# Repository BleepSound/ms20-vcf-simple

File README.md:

[![CC BY-SA 4.0][cc-by-sa-shield]][cc-by-sa]

# MS20 VCF

Latest documentation available at https://bleepsound.github.io/modules/

[![CC BY-SA 4.0][cc-by-sa-image]][cc-by-sa]

[cc-by-sa]: http://creativecommons.org/licenses/by-sa/4.0/
[cc-by-sa-image]: https://licensebuttons.net/l/by-sa/4.0/88x31.png
[cc-by-sa-shield]: https://img.shields.io/badge/License-CC%20BY--SA%204.0-lightgrey.svg

[![CC BY-SA 4.0][cc-by-sa-shield]][cc-by-sa]

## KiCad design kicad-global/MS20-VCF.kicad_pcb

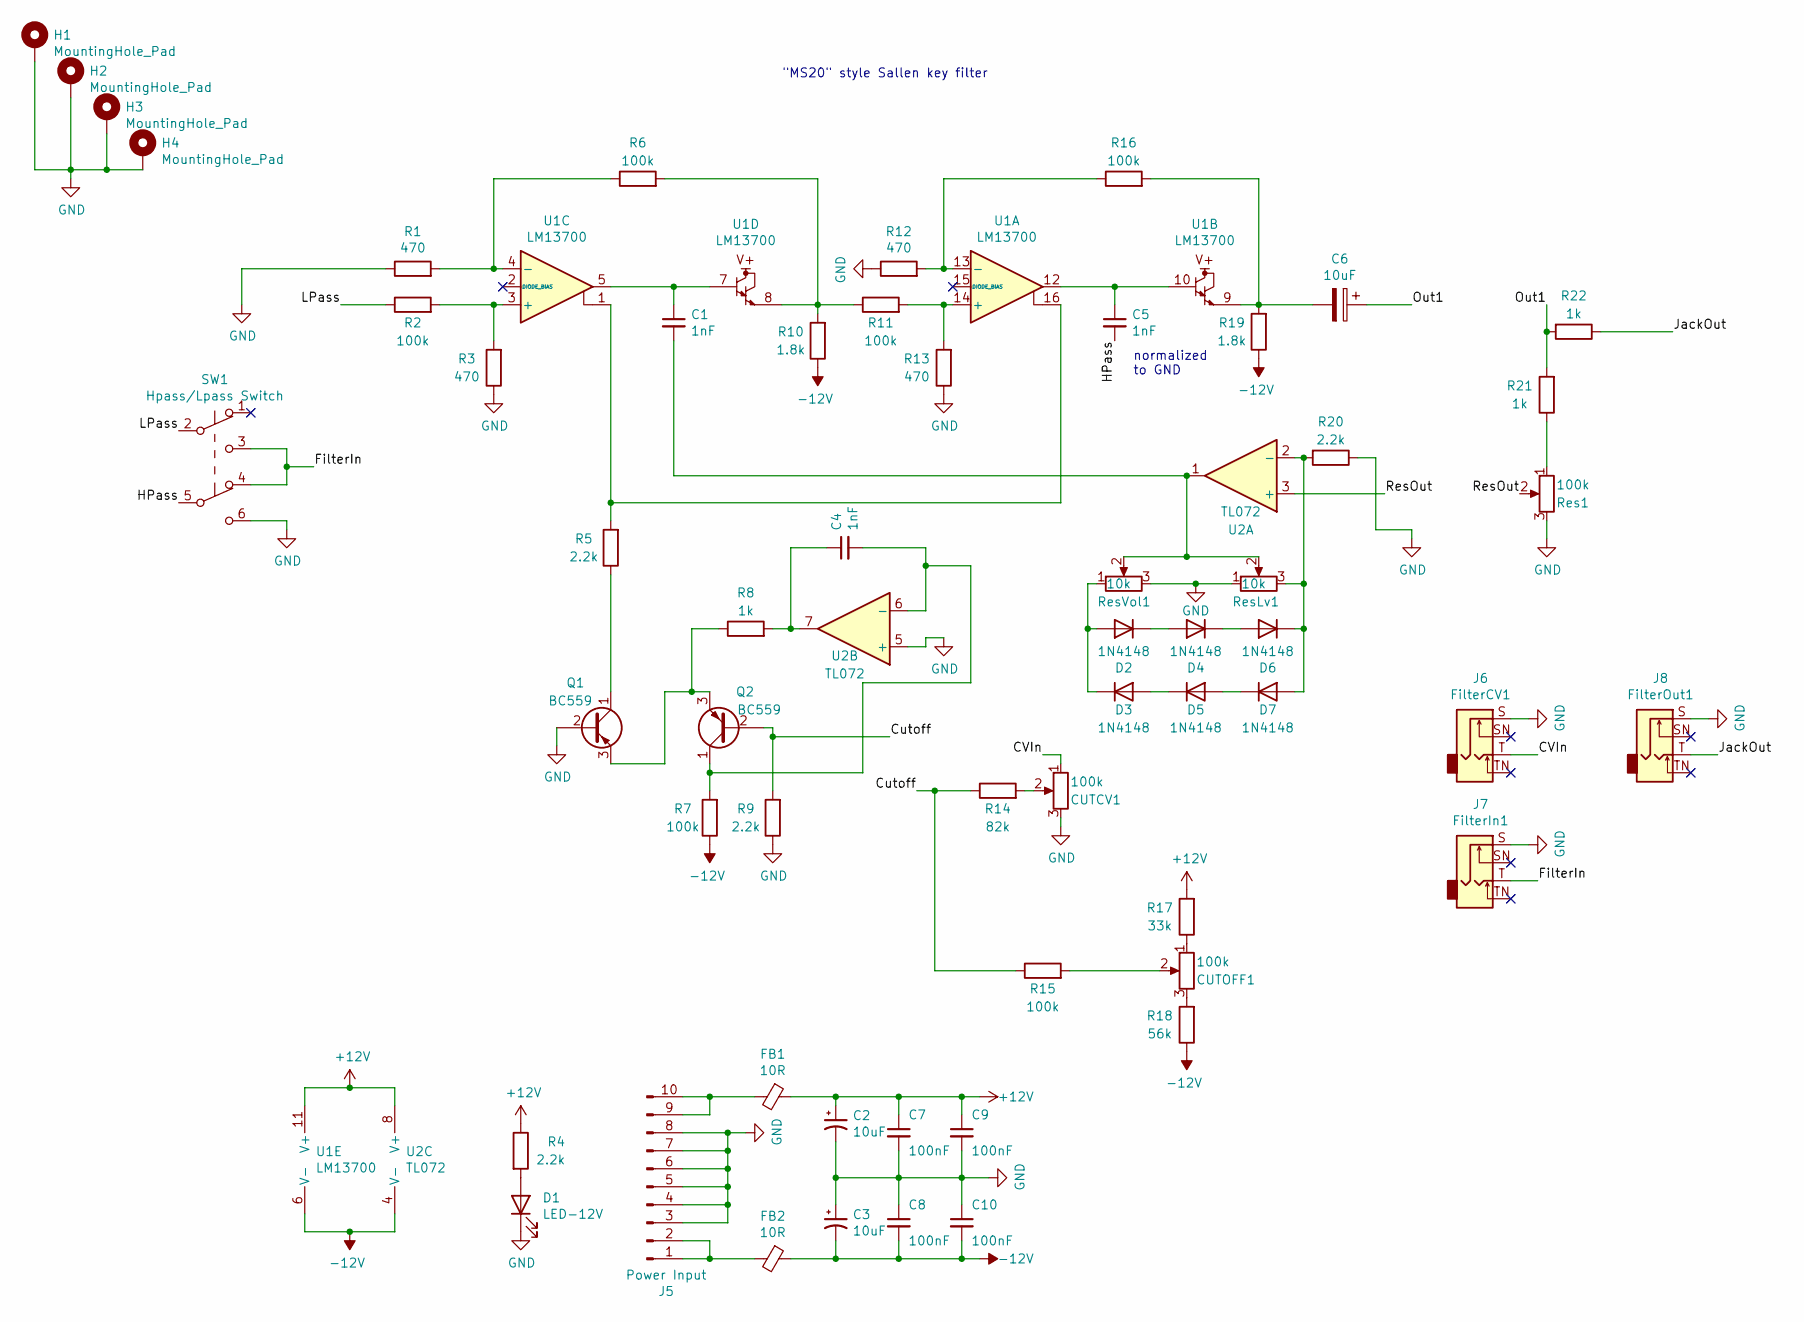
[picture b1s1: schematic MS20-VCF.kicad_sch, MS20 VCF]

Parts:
C1, C4, C5: 1nF; C_Disc_D7.0mm_W2.5mm_P5.00mm
C2, C3, C6: 10uF; CP_Radial_D5.0mm_P2.00mm
C7, C8, C9, C10: 100nF; C_Disc_D7.0mm_W2.5mm_P5.00mm
CUTCV1: 100k; Pot-bourns-alpha
CUTOFF1: 100k; Pot-bourns-alpha
D1: LED-12V; LED_D4.0mm
D2, D3, D4, D5, D6, D7: 1N4148; D_DO-35_SOD27_P7.62mm_Horizontal
FB1, FB2: 10R; L_Axial_L9.5mm_D4.0mm_P12.70mm_Horizontal_Fastron_SMCC
H1, H2, H3, H4: MountingHole_Pad; Doepfer Mounting hole
J5: Power Input; IDC-Header_2x05_P2.54mm_Vertical
J6: FilterCV1; Thonkiconn
J7: FilterIn1; Thonkiconn
J8: FilterOut1; Thonkiconn
Q1, Q2: BC559; TO-92_Inline_Wide
R1, R3, R12, R13: 470; R_Axial_DIN0207_L6.3mm_D2.5mm_P10.16mm_Horizontal
R2, R6, R7, R11, R15, R16: 100k; R_Axial_DIN0207_L6.3mm_D2.5mm_P10.16mm_Horizontal
R4, R5, R9, R20: 2.2k; R_Axial_DIN0207_L6.3mm_D2.5mm_P10.16mm_Horizontal
R8, R21, R22: 1k; R_Axial_DIN0207_L6.3mm_D2.5mm_P10.16mm_Horizontal
R10, R19: 1.8k; R_Axial_DIN0207_L6.3mm_D2.5mm_P10.16mm_Horizontal
R14: 82k; R_Axial_DIN0207_L6.3mm_D2.5mm_P10.16mm_Horizontal
R17: 33k; R_Axial_DIN0207_L6.3mm_D2.5mm_P10.16mm_Horizontal
R18: 56k; R_Axial_DIN0207_L6.3mm_D2.5mm_P10.16mm_Horizontal
Res1: 100k; Pot-bourns-alpha
ResLv1: 10k; Potentiometer_Bourns_3386C_Horizontal
ResVol1: 10k; Potentiometer_Bourns_3386C_Horizontal
SW1: Hpass/Lpass Switch; SW_DPDT_Toggle
U1: LM13700; SOIC-16_3.9x9.9mm_P1.27mm
U2: TL072; DIP-8_W7.62mm_Socket

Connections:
+12V: C2.1, C7.1, C9.1, FB1.1, R4.1, R17.2, U1.11 (V+), U2.8 (V+)
-12V: C3.2, C8.2, C10.2, FB2.1, R7.1, R10.1, R18.1, R19.1, U1.6 (V-), U2.4 (V-)
/CVIn: CUTCV1.1, J6.T
/Cutoff: Q2.2 (B), R9.2, R14.1, R15.1
/FilterIn: J7.T, SW1.3 (C), SW1.4 (A)
/HPass: C5.2, SW1.5 (B)
/JackOut: J8.T, R22.1
/LPass: R2.1, SW1.2 (B)
/Out1: C6.1, R21.2, R22.2
/ResOut: Res1.2, U2.3 (+)
GND: C2.2, C3.1, C7.2, C8.1, C9.2, C10.1, CUTCV1.3, D1.1 (K), H1.1, H2.1, H3.1, H4.1, J5.3, J5.4, J5.5, J5.6, J5.7, J5.8, J6.S, J7.S, J8.S, Q1.2 (B), R1.1, R3.1, R9.1, R12.1, R13.1, R20.1, Res1.3, ResLv1.1, ResVol1.3, SW1.6 (C), U2.5 (+)
unnamed: C1.1, U1.5, U1.7
unnamed: C1.2, ResLv1.2, ResVol1.2, U2.1
unnamed: C4.1, R8.2, U2.7
unnamed: C4.2, Q2.1 (C), R7.2, U2.6 (-)
unnamed: C5.1, U1.10, U1.12
unnamed: C6.2, R16.2, R19.2, U1.9
unnamed: CUTCV1.2, R14.2
unnamed: CUTOFF1.1, R17.1
unnamed: CUTOFF1.2, R15.2
unnamed: CUTOFF1.3, R18.2
unnamed: D1.2 (A), R4.2
unnamed: D2.1 (K), D4.2 (A)
unnamed: D2.2 (A), D3.1 (K), ResVol1.1
unnamed: D3.2 (A), D5.1 (K)
unnamed: D4.1 (K), D6.2 (A)
unnamed: D5.2 (A), D7.1 (K)
unnamed: D6.1 (K), D7.2 (A), R20.2, ResLv1.3, U2.2 (-)
unnamed: FB1.2, J5.9, J5.10
unnamed: FB2.2, J5.1, J5.2
unnamed: Q1.1 (C), R5.1
unnamed: Q1.3 (E), Q2.3 (E), R8.1
unnamed: R1.2, R6.1, U1.4 (-)
unnamed: R2.2, R3.2, U1.3 (+)
unnamed: R5.2, U1.1, U1.16
unnamed: R6.2, R10.2, R11.1, U1.8
unnamed: R11.2, R13.2, U1.14 (+)
unnamed: R12.2, R16.1, U1.13 (-)
unnamed: R21.1, Res1.1

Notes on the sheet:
normalized to GND
"MS20" style Sallen key filter

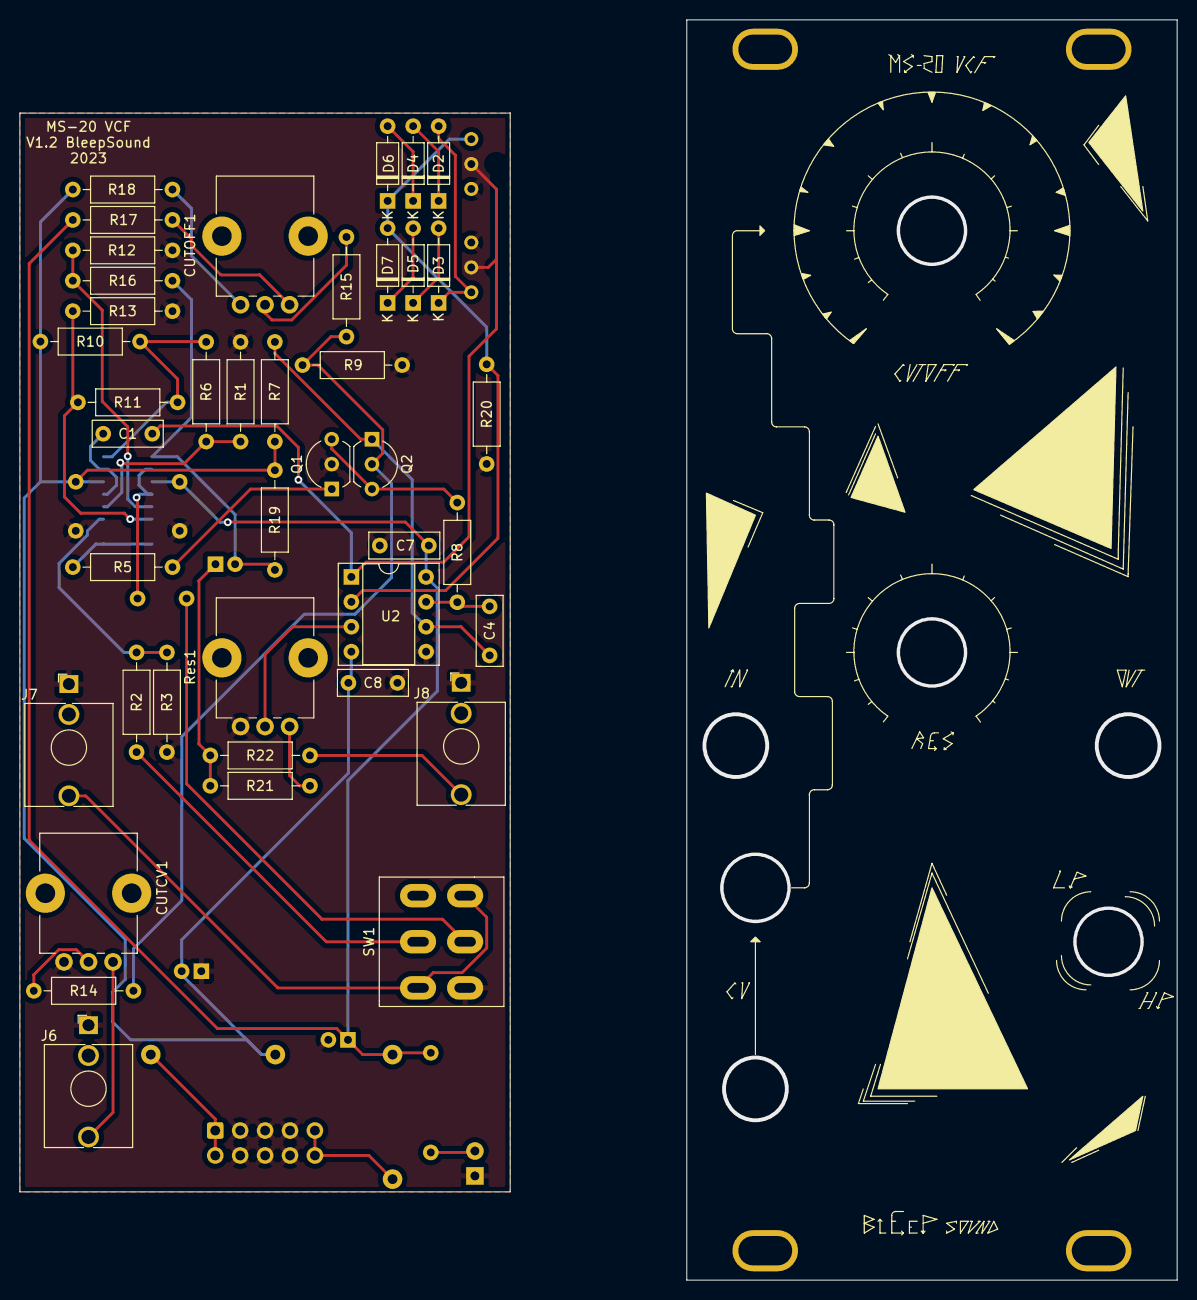
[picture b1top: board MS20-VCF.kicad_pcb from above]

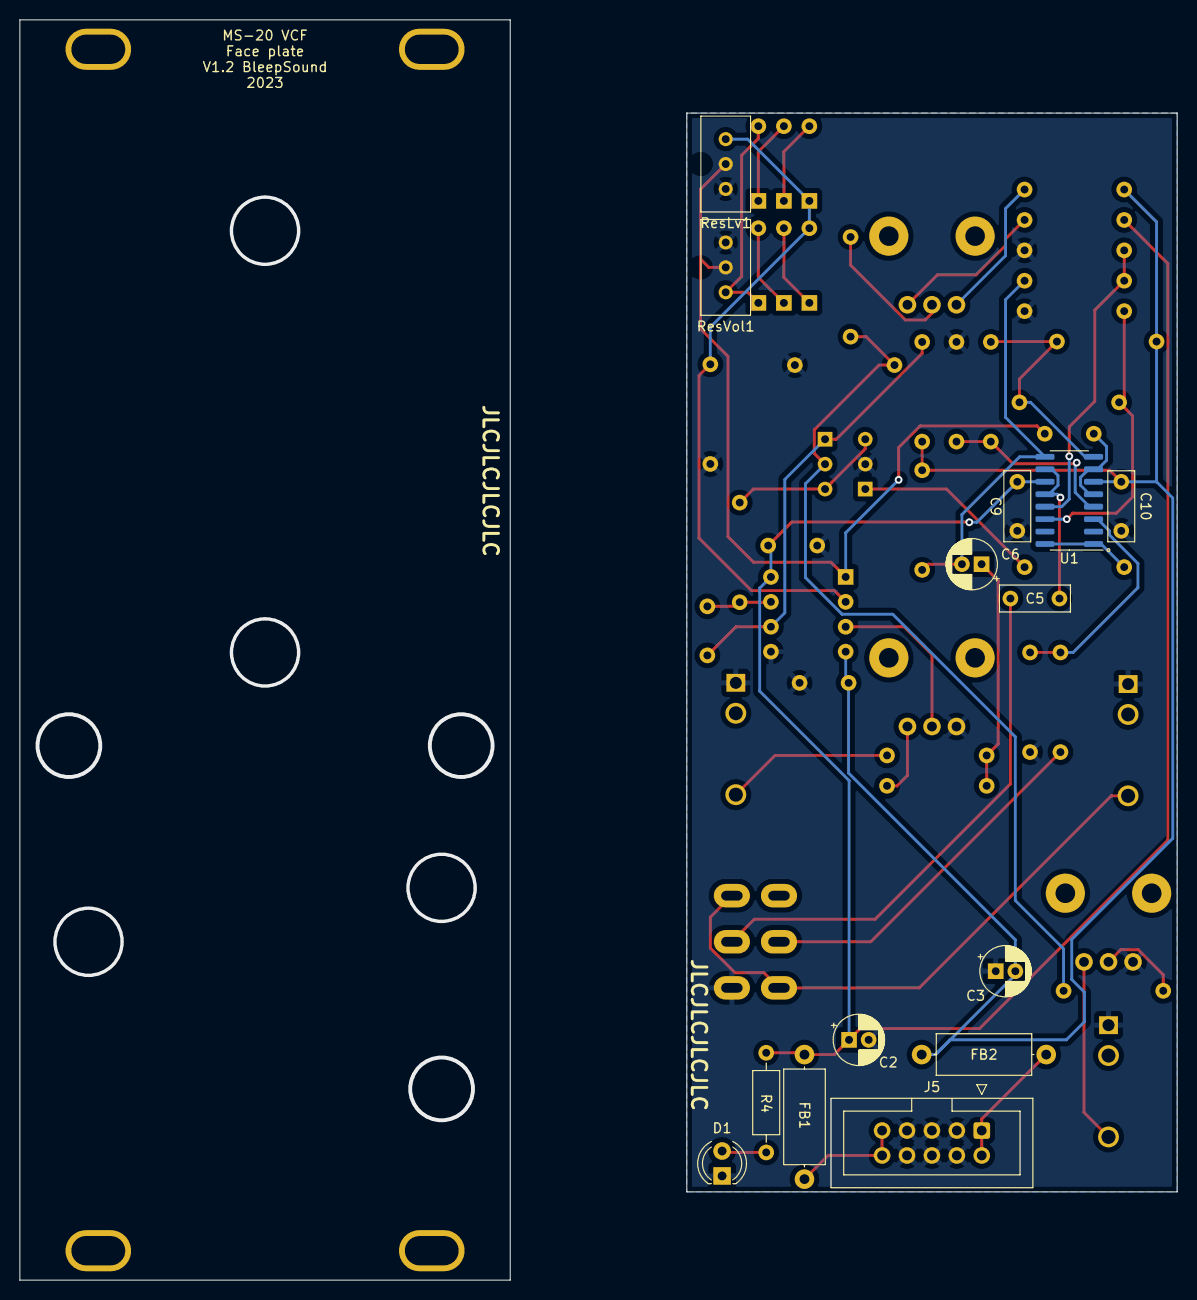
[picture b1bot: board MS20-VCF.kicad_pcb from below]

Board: 2 copper layers, 118.0 x 128.5 mm, 59 parts (14 on the bottom side), 39 nets.

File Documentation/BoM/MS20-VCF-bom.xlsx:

|  | KiBot Bill of Materials
 |  | Schematic: | MS20-VCF | Component Groups: | 24
 |  | Variant: | default | Component Count: | 55 (1 SMD/ 54 THT)
 |  | Revision: |  | Fitted Components: | 55 (1 SMD/ 54 THT)
 |  | Date: | 2023-01-12_18-05-41 | Number of PCBs: | 1
 |  | KiCad Version: | 6.0.10+dfsg-1~bpo11+1 | Total Components: | 55
Row | Description | References | Value | Quantity Per PCB | Comment
1 | Unpolarized capacitor, small symbol | C1 C4 C5 | 1nF | 3
2 | Unpolarized capacitor, small symbol | C7 C8 C9 C10 | 100nF | 4
3 |  | C2 C3 | 10µ | 2
4 |  | C6 | 10µF | 1
5 |  | CUTCV1 CUTOFF1 Res1 | 100k | 3
6 | Diode | D2 D3 D4 D5 D6 D7 | 1N4148 | 6
7 | Light emitting diode | D1 | LED-12V | 1
8 |  | FB1 FB2 | 10R | 2
9 | Audio Jack, 2 Poles (Mono / TS), Switched Pole (Normalling) | J6 J7 J8 | FilterCV1 | 3
10 | Generic connector, single row, 01x10, script generated (kicad-library-utils/sch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 | J5 | Power Input | 1
11 | 0.1A Ic, 30V Vce, PNP Small Signal Transistor, TO-92 | Q1 Q2 | BC559 | 2
12 | Resistor | R1 R3 R12 R13 | 470 | 4
13 | Resistor | R8 R21 R22 | 1k | 3
14 | Resistor | R10 R19 | 1.8k | 2
15 | Resistor | R4 R5 R9 R20 | 2.2k | 4
16 | Resistor | R17 | 33k | 1
17 | Resistor | R18 | 56k | 1
18 | Resistor | R14 | 82k | 1
19 | Resistor | R2 R6 R7 R11 R15 R16 | 100k | 6
20 |  | ResLv1 | 3.3k | 1
21 |  | ResVol1 | 10k | 1
22 | Momentary Switch, dual pole double throw | SW1 | Hpass/Lpass Switch | 1
23 | Dual Operational Transconductance Amplifiers with Linearizing Diodes and Buffer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 | U1 | LM13700 | 1
24 | Dual Low-Noise JFET-Input Operational Amplifiers, DIP-8/SOIC-8 | U2 | TL072 | 1

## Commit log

2022-12-11 test workflow (missing kibot conf files)
2022-12-13 init commit with base files (kibot files empty)
2022-12-13 config yaml not finished
2022-12-19 update workflow
2022-12-19 fix typo blocking workflow
2022-12-19 update env variables
2022-12-19 fix indent issue
2022-12-19 fix file names
2022-12-19 update path to files
2022-12-20 change artifact name + fix .sch path
2022-12-20 update deprecated commands
2022-12-20 fix last deprecated commands
2022-12-21 add gerber workflow
2022-12-21 add main BoM and images
2022-12-21 add comit for jack bom
2022-12-21 add jack BoM
2022-12-28 Add custom 3d models
2022-12-28 comment tag line for commit
2022-12-28 comment useless gerber gen
2022-12-28 add commit to gerber + comment useless tag
2022-12-28 Add pull to workflows to fix issue
2022-12-28 add ff option to pull
2022-12-28 add front gerber
2022-12-28 fix gerber gen files
2022-12-28 add jack gerber
2022-12-28 fix issue of folder creqtions
2022-12-28 fix naming issue
2023-01-09 add readme
2023-01-10 add populate manual
2023-01-10 fix indent typo
2023-01-10 change input file dir
2023-01-10 change output type
2023-01-10 change output to pcbdraw
2023-01-10 add render 3d correctly
2023-01-10 fix indent
2023-01-10 Remove ms20_vcf/simple/ from permalink
2023-01-11 move populate to have only concerned board
2023-01-11 trying to fix issue with populate comd
2023-01-11 update readme and kicab pcb for jackboard (fix 3d parts issue)
2023-01-11 add details and fix typos
2023-01-11 update excel bom conf
2023-01-12 add details and fix issues
2023-01-12 modif lowercase dir
2023-01-12 lowercase dir
2023-01-12 Add theme
2023-01-13 update bom gen
2023-01-15 Run build on push but deploy only in main
2023-01-15 Fix jemoji
2023-01-15 Fix jekyll build job
2023-01-15 Setup ruby
2023-01-15 Use gem theme instead of remote_theme
2023-01-15 update footprint trimmer
2023-01-15 add extra silkscreen info for smd components
2023-01-15 update to v1.2 on silkscreen
2023-02-18 update footprint for trimmer
2023-02-18 update readme with size in HP
2023-02-18 update workflow to work on push
2023-02-18 fix syntax error
2024-10-19 update repo organization
2024-10-26 Stop github pages hosting
2025-11-27 add licence
